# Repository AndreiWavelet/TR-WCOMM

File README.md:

# TR-WCOMM
This is an electronics and firmware project for a wireless file transmission device based on STM32L051 MCU and NRF24L01+ Transceiver. It's goal is to be small, low power, easy to use, easy to manufacture and to be able to send files over a outdoors distance of at least 100m. 

## What is looks like and how it works

The device is a small PCB with three LEDs in green, yellow and red, a push button, a SD Card socket and a U.FL antenna connector. There is space for mounting a battery connector ou  directly soldering battery leads to the PCB.

Once there is power, the user must connect the antenna and the SD Card press once the push button. All three leds will flash thrice, indicating that the device is on. Then, the user can press the button briefly (<1s) to activate the file transmission. Another identical device can be used to receive the file. If the user presses the button for more than 3s, it will power off, flashing all leds 4 times.

By default, it will send the file "data.dat" at the root of the SD Card, but if user implements the file "wcomm.cfg" at the root of the SD Card, the name of the transmitted file, along with some other configuration, can be changed.

### wcomm.cfg file example

```
Example wcomm.cfg
file = myfile.bin
dest = 12345
addr = 23568
ch = 10
```

### wcomm.cfg attributes

|Attribute  |Meaning                                            |
|:---------:|:-------------------------------------------------:|
|file       |Name of the file to be sent.                       |
|dest       |Destination address, up to 5 characters.           |
|addr       |Device address for reception, up to 5 characters.  |
|ch         |Channel to transmit and receive, 0-127.            |

### LED Functions

Each led will flash in response to a successul operation, a warning or an error.

|LED Color  |Meaning                                                                                  |
|:---------:|:---------------------------------------------------------------------------------------:|
|Green      |A successful operation has been completed, or the device is in a safe working condition. |
|Yellow     |There has been an error but the device has recovered, or the battery is weak.            |
|Red        |There has been an unrecoverable error (eg. SD Card failure)                              |

## Project Structure

The electronic schematics and board layout are located at the directory "Circuit" and the firmware code is located at the directory "Firmware". The electronic design was made with KiCad 5.1.12 and it's default libraries. The firmware design was made with STM32CubeIDE 1.9.0 and can be easily built with it. The firmware structure is further divided:

|Firmware Folder| Contents                                                                               |
|:-------------:|:--------------------------------------------------------------------------------------:|
|Application    |The main application code, with the vast majority of code writen by me.                 |
|Core           |Device initialization code generated automatically by STM32CubeIDE  .                   |
|Drivers        |Device drivers generated automatically by STM32CubeIDE.                                 |
|FATFS          |FatFs library diskio functions, mostly generated automatically by STM32CubeIDE.         |
|Middlewares    |Middleware code generated by STM32CubeIDE.                                              |

## Principles of working

The device power is expected to be fed by a 3.7 V battery. This voltage is regulated to 3.3 V to power all the board. A transistor connected to both a MCU pin and the push button allows power to flow from the battery to the rest of the circuit. The device is built around a STM32L051 MCU. The SD Card and the NRF24L01+ share the same SPI bus.

The main firmware part is written in C++17 and uses a simple cooperative task architecture with methods Setup() and Loop(). Once the method Setup() of all tasks are called, the core proceeds to call every Loop() function forever. Usually, inside every Loop() function, a state-machine is built using switch statements.

The firmware is divided in two parts: drivers and applications. The drivers abstract the hardware in a modular way, exposing easy to use methods for each device. The applications make use of drivers to produce useful output.

### Drivers Description

|Driver         | Description                                                                            |
|:-------------:|:--------------------------------------------------------------------------------------:|
|Battery        |Samples battery voltage and inform other tasks when it is too low.                      |
|Leds           |Controls the LEDs operation.                                                            |
|NRF24L01p      |Setups and controls NRF24L01+ Transceiver IC.                                           |
|Power          |Provide useful functions for low-power sleep and shutdown.                              |
|SpiManager     |Manages the shared SPI bus between SD Card and NRF24L01+.                               |
|Switches       |Provides the push button functionality with debounce and callback.                      |

### Applications Description

|Application    | Description                                                                            |
|:-------------:|:--------------------------------------------------------------------------------------:|
|Control        |Controls the main functionality of the device: file transmission and power.             |
|Main           |Simple task scheduler.                                                                  |
|SDCard         |Provides abstraction to SD Card access to files.                                        |
|TaskInterface  |Provides a standard interface for tasks to inherit from.                                |
|Tasks          |List of tasks.                                                                          |
|TickTimer      |Simple, easy to use, timer to measure milliseconds ticks.                               |

### Low Power Features

The device features a low power oriented design. The SD Card can be turned off by a transistor to save power, and the microcontroller will go to low power stop mode when in idle state, waking up every 3 seconds, listening for any data for 1 second, and then going low power again. The NRF24L01+ Transceiver was choosen for being design-proven, flexible and, most importantly, low power.

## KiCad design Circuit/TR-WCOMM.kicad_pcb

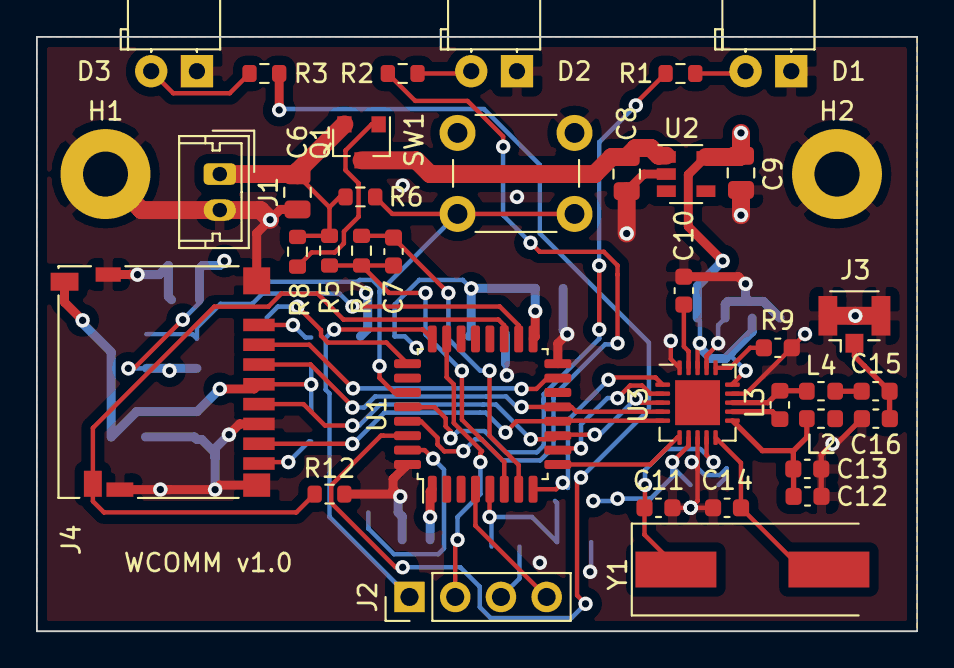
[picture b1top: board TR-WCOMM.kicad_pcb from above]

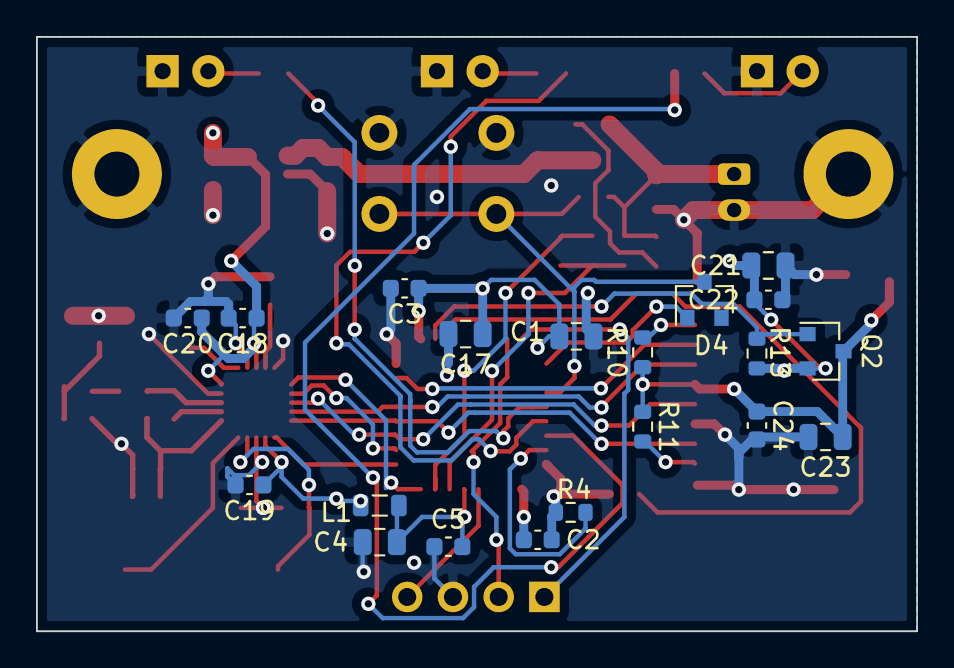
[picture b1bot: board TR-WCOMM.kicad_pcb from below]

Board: 4 copper layers, 48.9 x 33.0 mm, 58 parts (20 on the bottom side), 40 nets.

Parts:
C1, C4, C6, C8, C9, C17, C21, C23: 2u; C_0805_2012Metric
C2, C3, C5, C18, C19, C20, C22, C24: 100n; C_0603_1608Metric
C7: 1n; C_0603_1608Metric
C10: 33n; C_0603_1608Metric
C11, C14: 24p NPO; C_0603_1608Metric
C12: 2.2n; C_0603_1608Metric
C13: 4.7p NPO; C_0603_1608Metric
C15: 1.5p NPO; C_0603_1608Metric
C16: 1p NPO; C_0603_1608Metric
D1: LED G; LED_D5.0mm_Horizontal_O1.27mm_Z3.0mm
D2: LED Y; LED_D5.0mm_Horizontal_O1.27mm_Z3.0mm
D3: LED R; LED_D5.0mm_Horizontal_O1.27mm_Z3.0mm
D4: BAS19; SOT-23
H1, H2: MountingHole_Pad; MountingHole_2.5mm_Pad
J1: Conn_01x02; Molex_Micro-Latch_53253-0270_1x02_P2.00mm_Vertical
J2: Conn_01x04; PinHeader_1x04_P2.54mm_Vertical
J3: Conn_Coaxial; U.FL_Hirose_U.FL-R-SMT-1_Vertical
J4: Micro_SD_Card_Det; microSD_HC_Hirose_DM3D-SF
L1: 10u; L_0805_2012Metric
L2: 2.7n; L_0603_1608Metric
L3: 8.2n; L_0603_1608Metric
L4: 3.9n; L_0603_1608Metric
Q1, Q2: DMG2301L; SOT-23
R1, R2, R3: 100; R_0603_1608Metric
R4, R6, R10, R11, R12: 10k; R_0603_1608Metric
R5: 200k; R_0603_1608Metric
R7, R13: 100k; R_0603_1608Metric
R8: 570K; R_0603_1608Metric
R9: 22k; C_0603_1608Metric
SW1: SW_Push; SW_PUSH_6mm_H13mm
U1: STM32L041K6Tx; LQFP-32_7x7mm_P0.8mm
U2: TLV75533PDBV; SOT-23-5
U3: nRF24L01P; QFN-20-1EP_4x4mm_P0.5mm_EP2.5x2.5mm
Y1: 16M; Crystal_SMD_HC49-SD

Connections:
/3.3V: C1.1, C2.1, C3.1, C9.1, C17.1, C18.1, C19.1, C20.1, C21.1, C22.1, L1.1, Q2.2, R13.2, U1.1, U1.17, U2.5, U3.7, U3.15, U3.18
/GND: C1.2, C2.2, C3.2, C4.2, C5.2, C6.2, C8.2, C9.2, C10.2, C11.1, C12.2, C13.2, C14.2, C16.2, C17.2, C18.2, C19.2, C20.2, C21.2, C22.2, C23.2, C24.2, D1.1, D2.1, D3.1, H1.1, H2.1, J1.2, J2.3, J3.2, J4.6, J4.11, R4.2, R9.2, R12.2, SW1.1, U1.16, U1.32, U2.2, U3.8, U3.14, U3.17, U3.20
/MCU/BAT_FB: C7.1, R5.1, R7.1, U1.6
/MCU/LED_G: R1.1, U1.28
/MCU/LED_R: R3.1, U1.30
/MCU/LED_Y: R2.1, U1.29
/MCU/PWR_HOLD: D4.1, Q1.1, R8.1, U1.25
/MCU/SD_DET: J4.9, R12.1, U1.19
/MCU/SWCLK: J2.1, U1.24
/MCU/SWDIO: J2.2, U1.23
/MCU/VDDA: C4.1, C5.1, L1.2, U1.5
/MCU/~BAT_FB_EN: C7.2, R7.2, U1.7
/MCU/~PWR_BTN: D4.3, R6.2, SW1.2, U1.27
/MCU/~RST: J2.4, U1.4
/Power/VBAT+: C6.1, J1.1, Q1.2, R5.2, R6.1, R8.2
/SDCard/CS: J4.2, U1.15
/SDCard/DI: J4.3, U1.13, U3.4
/SDCard/DO: J4.7, U1.12, U3.5
/SDCard/SD_3.3V: C23.1, C24.1, J4.4, J4.10, Q2.3, R10.1, R11.1
/SDCard/~EN: Q2.1, R13.1, U1.18
/WirelessComm/CE: U1.8, U3.1
/WirelessComm/IRQ: U1.9, U3.6
/WirelessComm/SCK: J4.5, U1.11, U3.3
/WirelessComm/~CS: U1.10, U3.2
unnamed: C8.1, Q1.3, U2.1, U2.3
unnamed: C10.1, U3.19
unnamed: C11.2, U3.9, Y1.1
unnamed: C12.1, C13.1, L2.2, U3.11
unnamed: C14.1, U3.10, Y1.2
unnamed: C15.1, C16.1, J3.1
unnamed: C15.2, L4.2
unnamed: D1.2, R1.2
unnamed: D2.2, R2.2
unnamed: D3.2, R3.2
unnamed: J4.1, R10.2
unnamed: J4.8, R11.2
unnamed: L2.1, L3.2, U3.12
unnamed: L3.1, L4.1, U3.13
unnamed: R4.1, U1.31
unnamed: R9.1, U3.16

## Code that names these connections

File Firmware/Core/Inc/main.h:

/* USER CODE BEGIN Header */
/**
  ******************************************************************************
  * @file           : main.h
  * @brief          : Header for main.c file.
  *                   This file contains the common defines of the application.
  ******************************************************************************
  * @attention
  *
  * Copyright (c) 2022 STMicroelectronics.
  * All rights reserved.
  *
  * This software is licensed under terms that can be found in the LICENSE file
  * in the root directory of this software component.
  * If no LICENSE file comes with this software, it is provided AS-IS.
  *
  ******************************************************************************
  */
/* USER CODE END Header */

/* Define to prevent recursive inclusion -------------------------------------*/
#ifndef __MAIN_H
#define __MAIN_H

#ifdef __cplusplus
extern "C" {
#endif

/* Includes ------------------------------------------------------------------*/
#include "stm32l0xx_hal.h"

/* Private includes ----------------------------------------------------------*/
/* USER CODE BEGIN Includes */

/* USER CODE END Includes */

/* Exported types ------------------------------------------------------------*/
/* USER CODE BEGIN ET */

/* USER CODE END ET */

/* Exported constants --------------------------------------------------------*/
/* USER CODE BEGIN EC */

/* USER CODE END EC */

/* Exported macro ------------------------------------------------------------*/
/* USER CODE BEGIN EM */

/* USER CODE END EM */

/* Exported functions prototypes ---------------------------------------------*/
void Error_Handler(void);

/* USER CODE BEGIN EFP */

/* USER CODE END EFP */

/* Private defines -----------------------------------------------------------*/
#define BAT_FB_Pin GPIO_PIN_0
#define BAT_FB_GPIO_Port GPIOA
#define BAT_FB_nEN_Pin GPIO_PIN_1
#define BAT_FB_nEN_GPIO_Port GPIOA
#define RADIO_EN_Pin GPIO_PIN_2
#define RADIO_EN_GPIO_Port GPIOA
#define RADIO_IRQ_Pin GPIO_PIN_3
#define RADIO_IRQ_GPIO_Port GPIOA
#define RADIO_IRQ_EXTI_IRQn EXTI2_3_IRQn
#define RADIO_nCS_Pin GPIO_PIN_4
#define RADIO_nCS_GPIO_Port GPIOA
#define SD_nCS_Pin GPIO_PIN_1
#define SD_nCS_GPIO_Port GPIOB
#define SD_nEN_Pin GPIO_PIN_8
#define SD_nEN_GPIO_Port GPIOA
#define SD_DET_Pin GPIO_PIN_9
#define SD_DET_GPIO_Port GPIOA
#define SWDIO_Pin GPIO_PIN_13
#define SWDIO_GPIO_Port GPIOA
#define SWCLK_Pin GPIO_PIN_14
#define SWCLK_GPIO_Port GPIOA
#define PWR_HOLD_Pin GPIO_PIN_15
#define PWR_HOLD_GPIO_Port GPIOA
#define PWR_nBTN_Pin GPIO_PIN_4
#define PWR_nBTN_GPIO_Port GPIOB
#define PWR_nBTN_EXTI_IRQn EXTI4_15_IRQn
#define LED_G_Pin GPIO_PIN_5
#define LED_G_GPIO_Port GPIOB
#define LED_Y_Pin GPIO_PIN_6
#define LED_Y_GPIO_Port GPIOB
#define LED_R_Pin GPIO_PIN_7
#define LED_R_GPIO_Port GPIOB
/* USER CODE BEGIN Private defines */

/* USER CODE END Private defines */

#ifdef __cplusplus
}
#endif

#endif /* __MAIN_H */

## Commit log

2022-04-11 Add DOC dir.
2022-04-11 Add Board Render
2022-04-11 Add info to readme.
2022-04-11 Add circuit.
2022-04-11 Add base firmware.
2022-04-11 Add STM32 HAL Libraries.
2022-04-11 Add middlewares.
2022-04-11 Add hidden filles.
2022-04-11 Add hidden files.
2022-04-11 Adjust pinout.
